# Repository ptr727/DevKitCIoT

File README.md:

# DevKitCIoT

ESP32-DevKitC IoT controller board with a PSU, AC relay, dry contact inputs, and temperature sensor.

This board was originally designed in KiCad 5.99, a nightly pre-release of KiCad 6.0, with parts from a private part library. Version 0.2 was ordered from JLCPCB in September 2021. The design was later revamped for KiCad 10. Its parts were copied into a project-local library, so the repository is self-contained. The repository was then made public and archived. The design files are kept for reference, and no further changes are planned.

## Build and Distribution

- **Source Code**: [GitHub][github-link] for the KiCad design files, fabrication outputs, and CI pipelines.
- **Versioned Releases**: [GitHub Releases][releases-link] for version-tagged source code.

### Build Status

[![Build Status][buildstatus-shield]][actions-link]\
[![Last Commit][lastcommit-shield]][commits-link]

### Releases

[![GitHub Release][releaseversion-shield]][releases-link]\
[![GitHub Pre-Release][prereleaseversion-shield]][releases-link]

### Release Notes

**Version: 0.3**:

**Summary**:

- Migrated the design to KiCad 10, with every custom part in a project-local library.
- Updated every standard symbol and footprint to the KiCad 10 library, so ERC and DRC report no warnings.
- Regenerated the fabrication outputs and documentation from the KiCad 10 design.

> [!WARNING]
> **Breaking Changes**:
>
> - The design files are in the KiCad 10 format and do not open in earlier versions of KiCad.

See [Release History][history] for complete release notes and older versions.

## Table of Contents

- [Build and Distribution](#build-and-distribution)
  - [Build Status](#build-status)
  - [Releases](#releases)
  - [Release Notes](#release-notes)
- [Table of Contents](#table-of-contents)
- [Overview](#overview)
  - [GPIO](#gpio)
- [KiCad Setup](#kicad-setup)
- [Design](#design)
  - [Safety](#safety)
  - [Power Supply](#power-supply)
  - [Relay](#relay)
  - [Dry Contact Input](#dry-contact-input)
  - [DS18B20 Temperature Sensor](#ds18b20-temperature-sensor)
  - [PCB Terminal Connectors](#pcb-terminal-connectors)
  - [ESP32 DevKitC v4](#esp32-devkitc-v4)
  - [Enclosure](#enclosure)
- [Manufacturing](#manufacturing)
- [Questions or Issues](#questions-or-issues)
- [3rd Party Tools](#3rd-party-tools)
- [License](#license)

## Overview

> [!WARNING]
> The board switches mains AC voltage, with a danger of electrocution or fire.\
> Do not program the board while it is connected to AC power.\
> Use at your own risk.

This is an IoT controller board built around an [ESPRESSIF ESP32-DevKitC][esp32-devkitc-link] development board. It carries an onboard PSU, an AC relay, isolated dry contact inputs, and a DS18B20 temperature sensor.

[![3D Render][3d-small]][3d]\
[![PCB Layout][pcb-small]][pcb]

The [schematic][schematic] is available as a PDF. Firmware is out of scope for this repository. The GPIO assignments below are what a firmware configuration, such as [ESPHome][esphome-link], needs.

### GPIO

The [GPIO pins][esp32-gpio-link] are assigned based on [usage][esp32-pinout-link]:

- GPIO22 : Dallas 1-wire bus
- GPIO23 : Status output
- GPIO33 : Relay output
- GPIO34 : Dry contact input 1
- GPIO35 : Dry contact input 2

## KiCad Setup

- The project requires KiCad 10.0 or later, and the files are saved in the KiCad 10 format that earlier versions cannot open.
- The standard parts match the KiCad 10.0.7 libraries, the release CI checks against. Another point release can report library mismatch warnings.
- The custom symbols, footprints, and 3D models are in the project-local [`lib/`][lib] library, registered by the project's own [`sym-lib-table`][sym-lib-table] and [`fp-lib-table`][fp-lib-table] under the `DevKitCIoT` nickname.
- The custom 3D models are referenced through `${KIPRJMOD}`, so no global path variable or library registration is needed.
- The standard symbol, footprint, and 3D model libraries are bundled with KiCad 10 and registered automatically.

## Design

### Safety

The PCB layout keeps a clear separation between the AC and DC components and tracks. The board is not designed for high power applications, and the AC line input is protected with a 5A fuse. The PSU is isolated and safety certified, only the PSU and not the board, and does not require any external protection components.

### Power Supply

The 3W 5V PSU is a [RECOM RAC03-05SK][rac03-link], is very small, is safety certified, and does not require any external protection components.

### Relay

The relay is an [Omron G5Q][g5q-link] 10A miniature 5V relay. The relay driver is a [BS270][bs270-link] N-Channel MOSFET, with a [SB1H100][sb1h100-link] schottky diode for the snubber. For safety the load should be less than 5A, and the line input is protected with a 5A fuse.

### Dry Contact Input

The inputs are isolated using [ACPL-827][acpl-827-link] dual optoisolators. The dry contact inputs are pulled high to 5V, and close low to ground. Transistor output is pulled high to 3.3V, activating low to ground.

### DS18B20 Temperature Sensor

A [Dallas DS18B20][ds18b20-link] temperature sensor is mounted near the PSU to monitor board temperature. A connector allows connecting external DS18B20 sensors.

### PCB Terminal Connectors

The terminal connectors are [Phoenix SPTAF 1 EL][sptaf-link], using 5mm pitch for AC and 3.5mm pitch for signal.

### ESP32 DevKitC v4

The PCB can accommodate variants of the [ESPRESSIF ESP32-DevKitC v4][esp32-devkitc-link] boards, e.g. [ESP32-DevKitC-32E][esp32-wroom-32e-link] or [ESP32-DevKitCVE][esp32-wrover-e-link].

### Enclosure

The board is designed to fit a [Hammond RZ0212C][rz0212c-link] plastic enclosure.

## Manufacturing

The [`fabrication/`][fabrication] directory holds the Gerber, drill, and BOM files generated from the KiCad 10 design. The [Operations][operations] runbook has the `kicad-cli` commands that generate them. The BOM identifies a sourced part by its MPN, the manufacturer part number. It identifies a generic part by its CPL, a [Common Parts Library][cpl-link] or "jellybean" part number. The `JLCPCB_Y3-3712339A.zip` archive is the original version 0.2 order as submitted to [JLCPCB][jlcpcb-link] in 2021. The current design has the same copper layout as that order, apart from two changes the KiCad 10 library footprints brought. Pin 1 pads on C1, C3, D4, and U2 are rounded, along with their solder mask openings. U2 pads 5 and 7, R5 pad 2, and R9 pad 2 meet their copper pour through diagonal thermal spokes. The silkscreen also differs in the version and in the standard part outlines, which follow the KiCad 10 library. The title block differs too.

## Questions or Issues

This repository is archived and read-only, so it takes no new issues or pull requests. Earlier discussions remain readable in [GitHub Issues][issues-link].

## 3rd Party Tools

The third-party tools, libraries, and actions this project depends on.

- [cspell][cspell-link]: Spell checker.
- [editorconfig-checker][editorconfig-checker-link]: Line-ending and whitespace linter.
- [GitHub Actions][github-actions-link]: CI and automation runner.
- [GitHub Dependabot][dependabot-link]: Dependency update bot.
- [KiCad][kicad-link]: Open source electronic design automation suite.
- [kicad/kicad][kicad-docker-link]: Docker image providing `kicad-cli`.
- [markdownlint-cli2][markdownlint-link]: Markdown linter.
- [Nerdbank.GitVersioning][nbgv-link]: Version computation from git height.
- [pre-commit][pre-commit-link]: Git hook manager.
- [PyMuPDF][pymupdf-link]: Python library for rendering and reading PDF files.
- [uv][uv-link]: Python package and project manager.

## License

Licensed under the [MIT License][license]\
![GitHub License][license-shield]

The MIT license covers the author's original work, the circuit design and board layout included, and permits commercial use. The symbols, footprints, and 3D models in [`lib/`][lib], apart from one hand-drawn graphic, come from manufacturers, third-party providers, or unrecorded sources. The schematic, board, and generated outputs embed or reproduce them. They remain the property of their respective owners under their own terms. No ownership is claimed over them, and the MIT license does not extend to them. They are included for non-commercial reference use only, as is and without warranty. Standard KiCad library content is used under the KiCad libraries' own license. See [Attribution][attribution] for the sources and terms.

<!-- Shields -->

[buildstatus-shield]: https://img.shields.io/github/actions/workflow/status/ptr727/DevKitCIoT/test-pull-request.yml?logo=github&label=Build
[lastcommit-shield]: https://img.shields.io/github/last-commit/ptr727/DevKitCIoT?logo=github&label=Last%20Commit
[license-shield]: https://img.shields.io/github/license/ptr727/DevKitCIoT?label=License
[prereleaseversion-shield]: https://img.shields.io/github/v/release/ptr727/DevKitCIoT?include_prereleases&filter=*-g*&label=GitHub%20Pre-Release&logo=github
[releaseversion-shield]: https://img.shields.io/github/v/release/ptr727/DevKitCIoT?logo=github&label=GitHub%20Release

<!-- Distribution -->

[actions-link]: https://github.com/ptr727/DevKitCIoT/actions
[commits-link]: https://github.com/ptr727/DevKitCIoT/commits/main
[github-link]: https://github.com/ptr727/DevKitCIoT
[issues-link]: https://github.com/ptr727/DevKitCIoT/issues
[releases-link]: https://github.com/ptr727/DevKitCIoT/releases

<!-- Repo -->

[3d]: ./docs/DevKitCIoT_3D.png
[3d-small]: ./docs/DevKitCIoT_3D_Small.png
[attribution]: ./ATTRIBUTION.md
[fabrication]: ./fabrication/
[fp-lib-table]: ./fp-lib-table
[history]: ./HISTORY.md
[lib]: ./lib/
[license]: ./LICENSE
[operations]: ./OPERATIONS.md
[pcb]: ./docs/DevKitCIoT_PCB.png
[pcb-small]: ./docs/DevKitCIoT_PCB_Small.png
[schematic]: ./docs/DevKitCIoT_Schematic.pdf
[sym-lib-table]: ./sym-lib-table

<!-- External -->

[acpl-827-link]: https://docs.broadcom.com/doc/AV02-1429EN
[bs270-link]: https://www.onsemi.com/download/data-sheet/pdf/bs270-d.pdf
[cpl-link]: https://octopart.com/common-parts-library
[cspell-link]: https://cspell.org
[dependabot-link]: https://github.com/dependabot
[ds18b20-link]: https://datasheets.maximintegrated.com/en/ds/DS18B20-PAR.pdf
[editorconfig-checker-link]: https://github.com/editorconfig-checker/editorconfig-checker
[esp32-devkitc-link]: https://www.espressif.com/en/products/devkits/esp32-devkitc
[esp32-gpio-link]: https://docs.espressif.com/projects/esp-idf/en/latest/esp32/api-reference/peripherals/gpio.html
[esp32-pinout-link]: https://docs.espressif.com/projects/esp-idf/en/latest/esp32/_images/esp32-devkitC-v4-pinout.jpg
[esp32-wroom-32e-link]: https://www.espressif.com/sites/default/files/documentation/esp32-wroom-32e_esp32-wroom-32ue_datasheet_en.pdf
[esp32-wrover-e-link]: https://www.espressif.com/sites/default/files/documentation/esp32-wrover-e_esp32-wrover-ie_datasheet_en.pdf
[esphome-link]: https://esphome.io/
[g5q-link]: https://omronfs.omron.com/en_US/ecb/products/pdf/en-g5q.pdf
[github-actions-link]: https://github.com/actions
[jlcpcb-link]: https://jlcpcb.com/
[kicad-docker-link]: https://hub.docker.com/r/kicad/kicad
[kicad-link]: https://www.kicad.org/
[markdownlint-link]: https://github.com/DavidAnson/markdownlint-cli2
[nbgv-link]: https://github.com/dotnet/Nerdbank.GitVersioning
[pre-commit-link]: https://pre-commit.com/
[pymupdf-link]: https://pymupdf.readthedocs.io/
[rac03-link]: https://recom-power.com/pdf/Powerline_AC-DC/RAC03-K.pdf
[rz0212c-link]: https://www.hammfg.com/part/RZ0212C
[sb1h100-link]: https://www.vishay.com/docs/88716/sb1h90.pdf
[sptaf-link]: https://www.phoenixcontact.com/assets/downloads_ed/local_us/web_dwl_promotion/SPTAF1_Flash_2017.pdf
[uv-link]: https://docs.astral.sh/uv/

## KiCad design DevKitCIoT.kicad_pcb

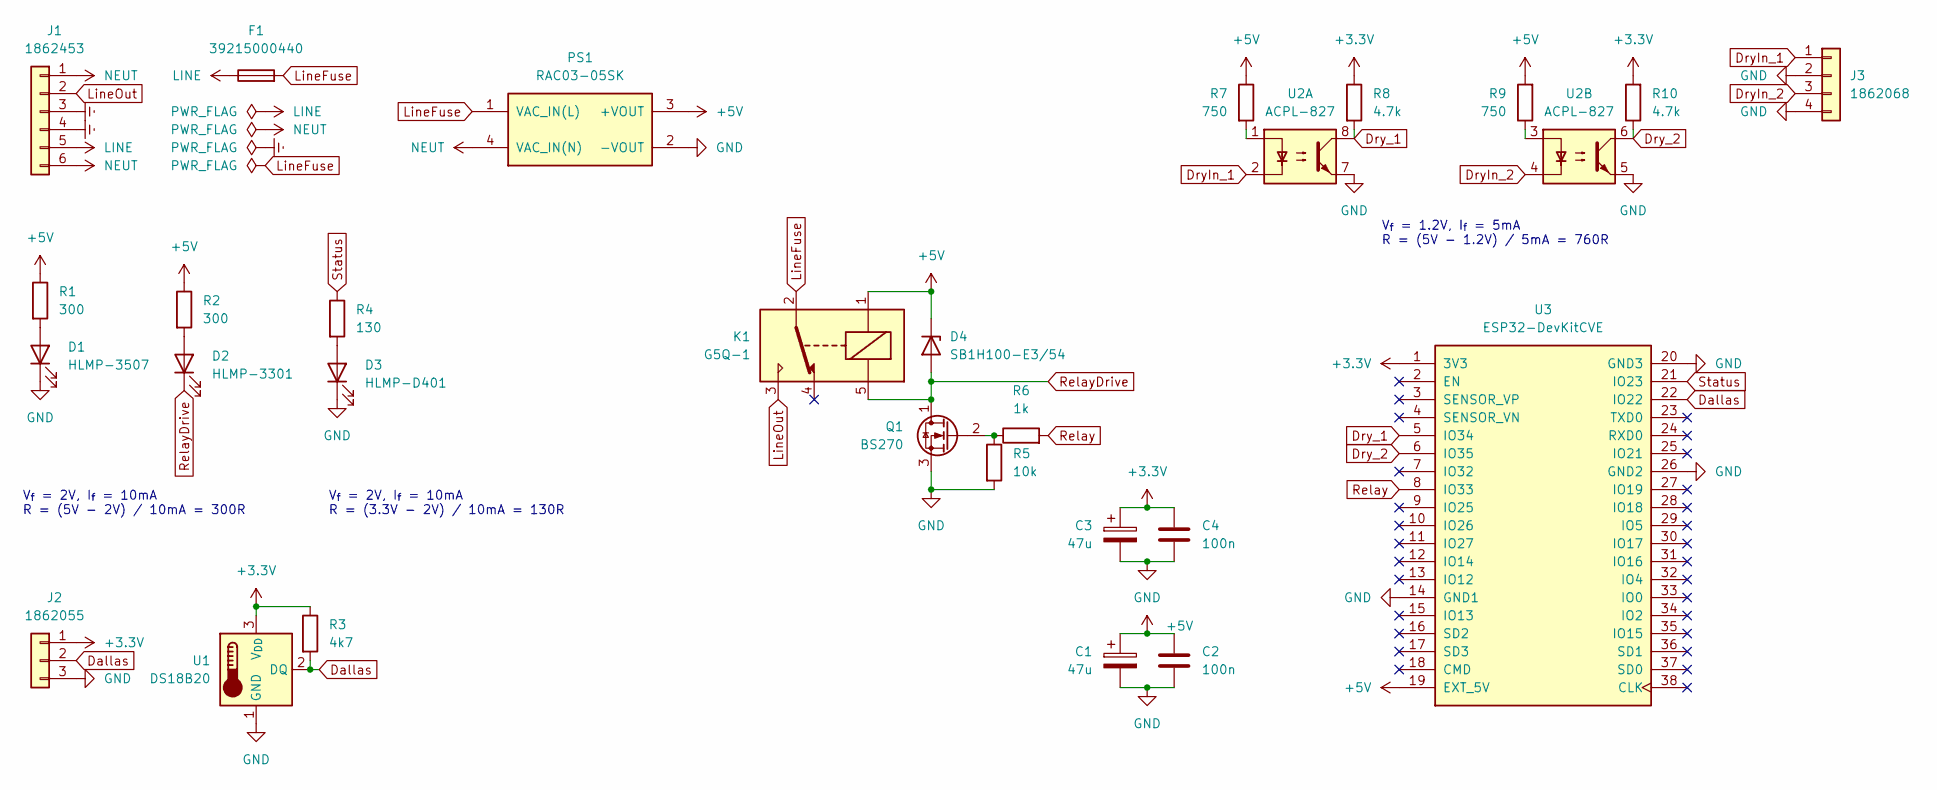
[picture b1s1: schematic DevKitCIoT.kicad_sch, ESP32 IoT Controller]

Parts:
C1, C3: 47u; CP_Radial_D5.0mm_P2.50mm
C2, C4: 100n; C_Disc_D3.0mm_W2.0mm_P2.50mm
D1: HLMP-3507; LED_D5.0mm; MPN HLMP-3507
D2: HLMP-3301; LED_D5.0mm; MPN HLMP-3301
D3: HLMP-D401; LED_D5.0mm; MPN HLMP-D401
D4: SB1H100-E3/54; D_DO-41_SOD81_P7.62mm_Horizontal; MPN SB1H100-E3/54
F1: 39215000440; Fuse_Littelfuse_392Series; MPN 39215000440
J1: 1862453; TerminalBlock_Phoenix_SPTAF-1-6-5.0-EL_1x06_P5.0mm_Horizont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; MPN 1862453
J2: 1862055; TerminalBlock_Phoenix_SPTAF-1-3-3.5-EL_1x03_P3.5mm_Horizont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; MPN 1862055
J3: 1862068; TerminalBlock_Phoenix_SPTAF-1-4-3.5-EL_1x04_P3.5mm_Horizont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; MPN 1862068
K1: G5Q-1; Relay_SPDT_Omron_G5Q-1; MPN G5Q-14 DC5
PS1: RAC03-05SK; Converter_ACDC_RECOM_RAC03-xxSK_THT; MPN RAC03-05SK
Q1: BS270; TO-92_Inline_Wide; MPN BS270
R1, R2: 300; R_Axial_DIN0207_L6.3mm_D2.5mm_P7.62mm_Horizontal
R3: 4k7; R_Axial_DIN0207_L6.3mm_D2.5mm_P7.62mm_Horizontal
R4: 130; R_Axial_DIN0207_L6.3mm_D2.5mm_P7.62mm_Horizontal
R5: 10k; R_Axial_DIN0207_L6.3mm_D2.5mm_P7.62mm_Horizontal
R6: 1k; R_Axial_DIN0207_L6.3mm_D2.5mm_P7.62mm_Horizontal
R7, R9: 750; R_Axial_DIN0207_L6.3mm_D2.5mm_P7.62mm_Horizontal
R8, R10: 4.7k; R_Axial_DIN0207_L6.3mm_D2.5mm_P7.62mm_Horizontal
U1: DS18B20; TO-92_Inline_Wide; MPN DS18B20+
U2: ACPL-827; DIP-8_W7.62mm; MPN ACPL-827-00CE
U3: ESP32-DevKitCVE; RF_Module_ESP32-DevKitC; MPN ESP32-DevKitCVE

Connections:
+3.3V: C3.1, C4.1, J2.1, R3.1, R8.1, R10.2, U1.3 (V_{DD}), U3.1 (3V3)
+5V: C1.1, C2.1, D4.1 (K), K1.1, PS1.3 (+VOUT), R1.1, R2.1, R7.1, R9.2, U3.19 (EXT_5V)
Dallas: J2.2, R3.2, U1.2 (DQ), U3.22 (IO22)
DryIn_1: J3.1, U2.2
DryIn_2: J3.3, U2.4
Dry_1: R8.2, U2.8, U3.5 (IO34)
Dry_2: R10.1, U2.6, U3.6 (IO35)
Earth: J1.3, J1.4
GND: C1.2, C2.2, C3.2, C4.2, D1.1 (K), D3.1 (K), J2.3, J3.2, J3.4, PS1.2 (-VOUT), Q1.3 (S), R5.2, U1.1 (GND), U2.5, U2.7, U3.14 (GND1), U3.20 (GND3), U3.26 (GND2)
LINE: F1.1, J1.5
LineFuse: F1.2, K1.2, PS1.1 (VAC_IN(L))
LineOut: J1.2, K1.3
NEUT: J1.1, J1.6, PS1.4 (VAC_IN(N))
unnamed: D1.2 (A), R1.2
unnamed: D2.2 (A), R2.2
unnamed: D3.2 (A), R4.2
unnamed: Q1.2 (G), R5.1, R6.1
unnamed: R7.2, U2.1
unnamed: R9.1, U2.3
Relay: R6.2, U3.8 (IO33)
RelayDrive: D2.1 (K), D4.2 (A), K1.5, Q1.1 (D)
Status: R4.1, U3.21 (IO23)

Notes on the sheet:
V_{f} = 2V, I_{f} = 10mA R = (3.3V - 2V) / 10mA = 130R
V_{f} = 1.2V, I_{f} = 5mA R = (5V - 1.2V) / 5mA = 760R
V_{f} = 2V, I_{f} = 10mA R = (5V - 2V) / 10mA = 300R

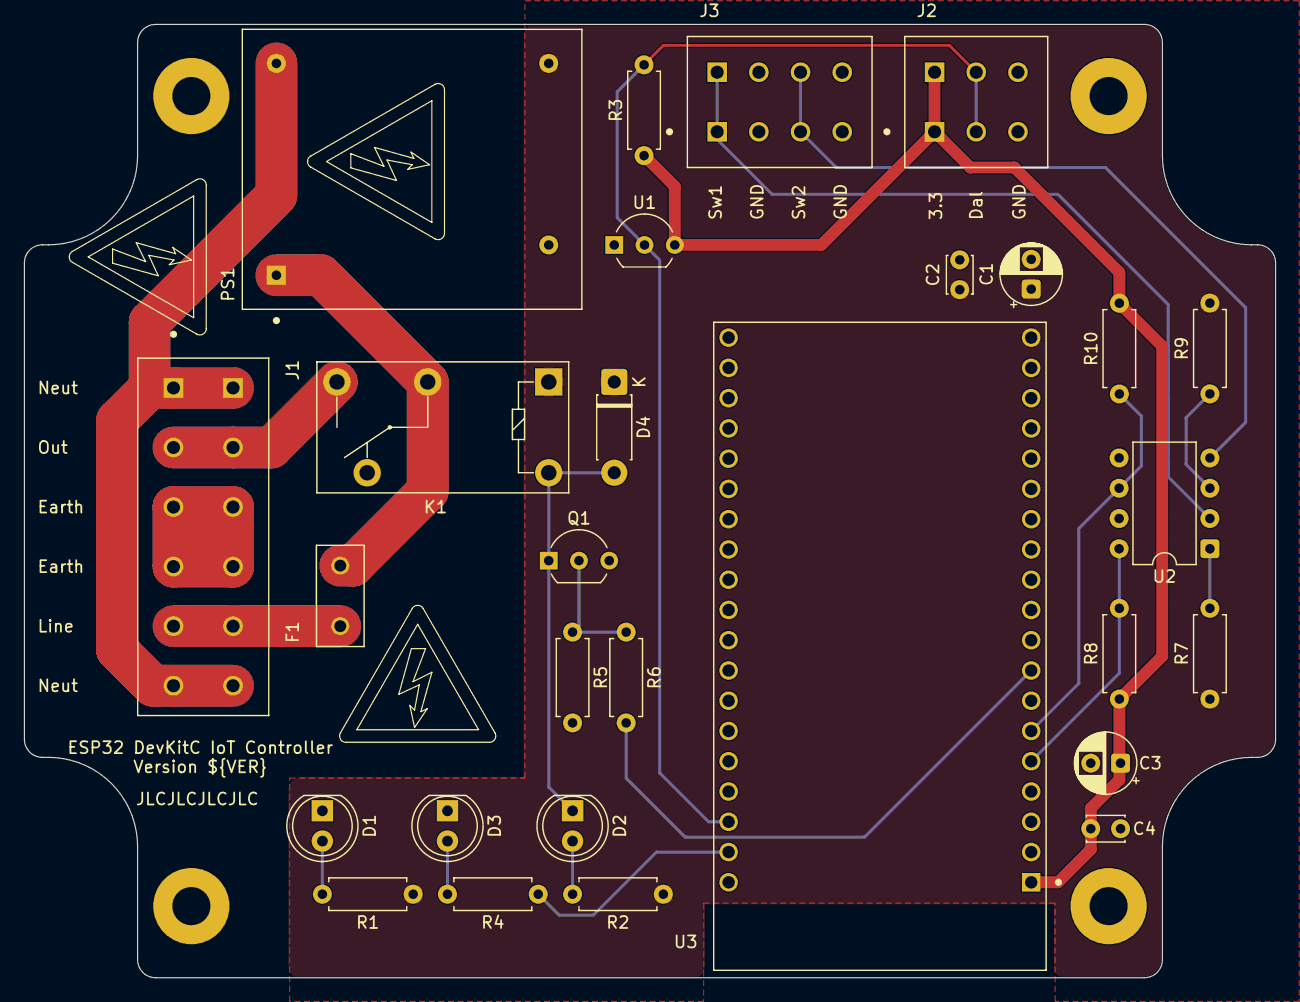
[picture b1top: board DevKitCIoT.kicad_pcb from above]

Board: 2 copper layers, 105.0 x 80.0 mm, 32 parts (0 on the bottom side), 22 nets.

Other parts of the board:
H1, H2, H3, H4: MountingHole; MountingHole_3.2mm_M3_Pad

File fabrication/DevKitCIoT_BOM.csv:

"References","Value","Footprint","Quantity","MPN","CPL"
"C1 C3","47u","Capacitor_THT:CP_Radial_D5.0mm_P2.50mm","2","","CPL-CAP-ALU-RAD-47UF-50V"
"C2 C4","100n","Capacitor_THT:C_Disc_D3.0mm_W2.0mm_P2.50mm","2","","100n 25V"
"D1","HLMP-3507","LED_THT:LED_D5.0mm","1","HLMP-3507",""
"D2","HLMP-3301","LED_THT:LED_D5.0mm","1","HLMP-3301",""
"D3","HLMP-D401","LED_THT:LED_D5.0mm","1","HLMP-D401",""
"D4","SB1H100-E3/54","Diode_THT:D_DO-41_SOD81_P7.62mm_Horizontal","1","SB1H100-E3/54",""
"F1","39215000440","DevKitCIoT:Fuse_Littelfuse_392Series","1","39215000440",""
"J1","1862453","DevKitCIoT:TerminalBlock_Phoenix_SPTAF-1-6-5.0-EL_1x06_P5.0mm_Horizontal","1","1862453",""
"J2","1862055","DevKitCIoT:TerminalBlock_Phoenix_SPTAF-1-3-3.5-EL_1x03_P3.5mm_Horizontal","1","1862055",""
"J3","1862068","DevKitCIoT:TerminalBlock_Phoenix_SPTAF-1-4-3.5-EL_1x04_P3.5mm_Horizontal","1","1862068",""
"K1","G5Q-1","DevKitCIoT:Relay_SPDT_Omron_G5Q-1","1","G5Q-14 DC5",""
"PS1","RAC03-05SK","DevKitCIoT:Converter_ACDC_RECOM_RAC03-xxSK_THT","1","RAC03-05SK",""
"Q1","BS270","Package_TO_SOT_THT:TO-92_Inline_Wide","1","BS270",""
"R1 R2","300","Resistor_THT:R_Axial_DIN0207_L6.3mm_D2.5mm_P7.62mm_Horizontal","2","","300 0.25W 5%"
"R3","4k7","Resistor_THT:R_Axial_DIN0207_L6.3mm_D2.5mm_P7.62mm_Horizontal","1","","4.7k 0.25W 5%"
"R4","130","Resistor_THT:R_Axial_DIN0207_L6.3mm_D2.5mm_P7.62mm_Horizontal","1","","130 0.25W 5%"
"R5","10k","Resistor_THT:R_Axial_DIN0207_L6.3mm_D2.5mm_P7.62mm_Horizontal","1","","10k 0.25W 5%"
"R6","1k","Resistor_THT:R_Axial_DIN0207_L6.3mm_D2.5mm_P7.62mm_Horizontal","1","","1k 0.25W 5%"
"R7 R9","750","Resistor_THT:R_Axial_DIN0207_L6.3mm_D2.5mm_P7.62mm_Horizontal","2","","750 0.25W 5%"
"R8 R10","4.7k","Resistor_THT:R_Axial_DIN0207_L6.3mm_D2.5mm_P7.62mm_Horizontal","2","","4.7k 0.25W 5%"
"U1","DS18B20","Package_TO_SOT_THT:TO-92_Inline_Wide","1","DS18B20+",""
"U2","ACPL-827","Package_DIP:DIP-8_W7.62mm","1","ACPL-827-00CE",""
"U3","ESP32-DevKitCVE","DevKitCIoT:RF_Module_ESP32-DevKitC","1","ESP32-DevKitCVE",""
